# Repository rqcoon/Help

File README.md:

# Help
Help! 25 Key Keyboard

<div style="width: 60%; height: 60%">

</div>

### !! BE WARNED, THIS IS UNTESTED !!

The Help! is a 9x3 ortholinear pro micro based keyboard. It has support for an SSD1306 OLED display that sits above the pro micro à la corne.

| TODO | status |
| ----------- | ----------- |
| Firmare | :x: |
| Case | :heavy_check_mark: |

### PCB Render:

### KLE:

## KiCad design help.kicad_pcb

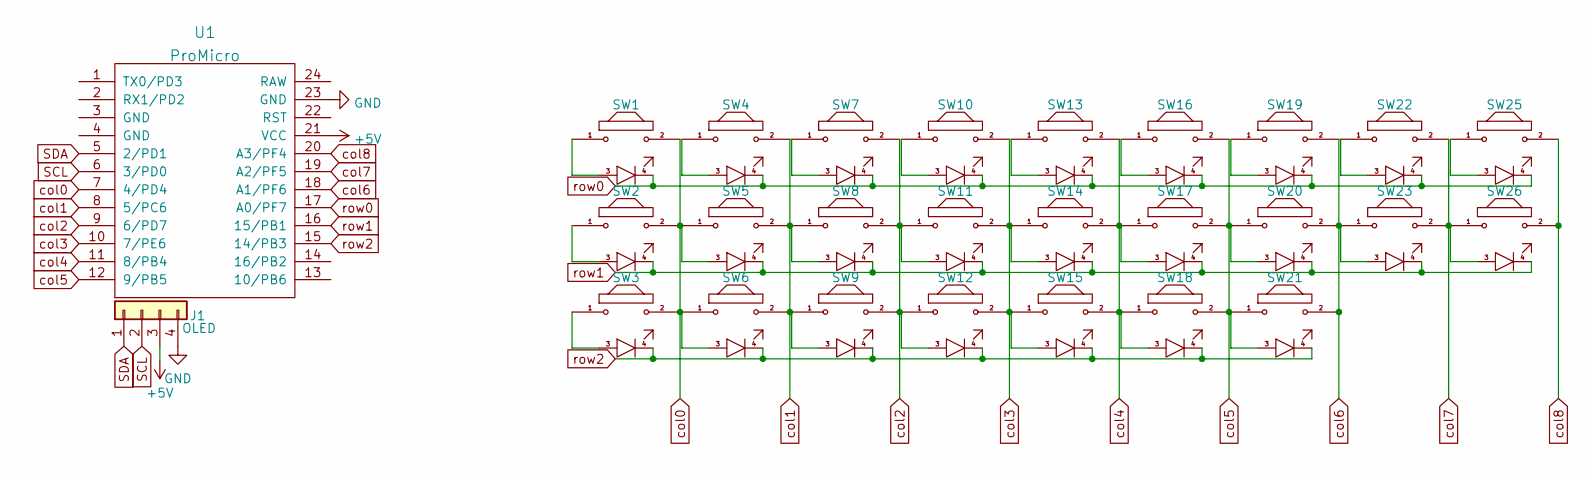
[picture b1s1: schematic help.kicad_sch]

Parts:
J1: OLED; PinSocket_1x04_P2.54mm_Vertical
SW1, SW2, SW3, SW4, SW5, SW6, SW7, SW8, SW9, SW10, SW11, SW12, SW13, SW14, SW15, SW16, SW17, SW18, SW19, SW20, SW21, SW22, SW23, SW25, SW26: MX; MX-Alps-Choc-1U
U1: ProMicro; ArduinoProMicro

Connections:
+5V: J1.3, U1.21 (VCC)
GND: J1.4, U1.23 (GND)
unnamed: SW1.1, SW1.3
unnamed: SW2.1, SW2.3
unnamed: SW3.1, SW3.3
unnamed: SW4.1, SW4.3
unnamed: SW5.1, SW5.3
unnamed: SW6.1, SW6.3
unnamed: SW7.1, SW7.3
unnamed: SW8.1, SW8.3
unnamed: SW9.1, SW9.3
unnamed: SW10.1, SW10.3
unnamed: SW11.1, SW11.3
unnamed: SW12.1, SW12.3
unnamed: SW13.1, SW13.3
unnamed: SW14.1, SW14.3
unnamed: SW15.1, SW15.3
unnamed: SW16.1, SW16.3
unnamed: SW17.1, SW17.3
unnamed: SW18.1, SW18.3
unnamed: SW19.1, SW19.3
unnamed: SW20.1, SW20.3
unnamed: SW21.1, SW21.3
unnamed: SW22.1, SW22.3
unnamed: SW23.1, SW23.3
unnamed: SW25.1, SW25.3
unnamed: SW26.1, SW26.3
SCL: J1.2, U1.6 (3/PD0)
SDA: J1.1, U1.5 (2/PD1)
col0: SW1.2, SW2.2, SW3.2, U1.7 (4/PD4)
col1: SW4.2, SW5.2, SW6.2, U1.8 (5/PC6)
col2: SW7.2, SW8.2, SW9.2, U1.9 (6/PD7)
col3: SW10.2, SW11.2, SW12.2, U1.10 (7/PE6)
col4: SW13.2, SW14.2, SW15.2, U1.11 (8/PB4)
col5: SW16.2, SW17.2, SW18.2, U1.12 (9/PB5)
col6: SW19.2, SW20.2, SW21.2, U1.18 (A1/PF6)
col7: SW22.2, SW23.2, U1.19 (A2/PF5)
col8: SW25.2, SW26.2, U1.20 (A3/PF4)
row0: SW1.4, SW4.4, SW7.4, SW10.4, SW13.4, SW16.4, SW19.4, SW22.4, SW25.4, U1.17 (A0/PF7)
row1: SW2.4, SW5.4, SW8.4, SW11.4, SW14.4, SW17.4, SW20.4, SW23.4, SW26.4, U1.16 (15/PB1)
row2: SW3.4, SW6.4, SW9.4, SW12.4, SW15.4, SW18.4, SW21.4, U1.15 (14/PB3)

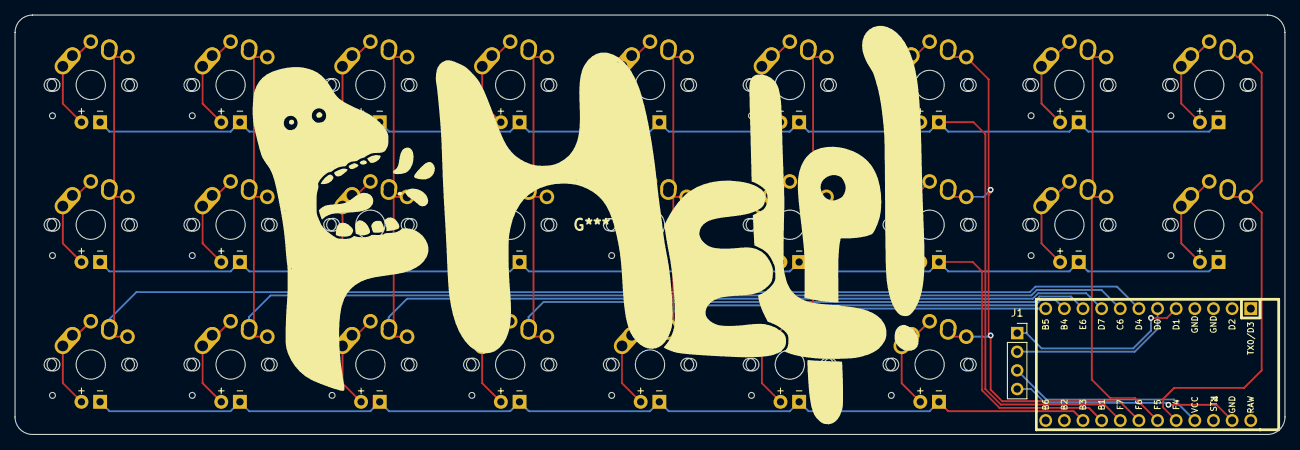
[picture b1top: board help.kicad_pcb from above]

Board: 2 copper layers, 173.0 x 57.2 mm, 27 parts (0 on the bottom side), 41 nets.

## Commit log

2022-01-01 Add Files
2022-01-01 Add Images
2022-01-01 gone
2022-01-01 Add PCB screenshots
2022-01-01 add KLE image
2022-01-01 Add Gerbers
    forgot not everyone uses kicad nightly sorry
2022-01-02 Create tmp
2022-01-02 Add case files
2022-01-03 Fixed bottom half
    Added more area for the underside of the PCB and fixed the tolerances for friction fitting
